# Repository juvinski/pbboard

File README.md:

# PocketBeagle 2 DIY Cape for Ardupilot
This project aim enable to run [Ardupilot](https://ardupilot.org/) on the [PocketBeagle 2](https://www.beagleboard.org/boards/pocketbeagle-2) Board.

# Board manufacturing
## PCBWay
I'm using the PCBWay to produce the boards - 5 boards have a cost of USD 5.00
You can use [this file](Board_Archives_Manufacturing/PocketPilot2.kicad_pcb.zip).

## Other Services
I believe the same file can be used by other online PCB manufactures.

# Board Images
## Board Only

## Board Components - Preview

# Hardware instructions
## Board manufacturing
### Board version 1.1

### Soldering resistors, transistor and rc output headers 

### Soldering output headers 

### Soldering Pocketbeagle 2 headers

### Soldering Leds

### Preparing the IMU - using double sided tape

### Soldering the IMU

### Finished

## Schematic
The schematic can be found [here](Schematic/PocketPilot2.pdf).

## Parts
	- 1 IMU [GY-912](https://www.ebay.com/itm/166809278501)
	- 4 Resistors 1KΩ
	- 2 Resistors 10k 0.1%
	- 2 Resistors 20k 0.1%
	- 3 Led Red, Blue and Green color 
	- 1 BC548 NPN Transistor
	- 1 I2C Digital [Power Module/Monitor](https://ardupilot.org/copter/docs/common-powermodule-landingpage.html#i2c-power-monitor)
	- 6 Pin header 1 x 5 straight
	- 3 Pin header 1 x 4 straight
	- 1 Pin header 1 x 6 straight
	- 6 Pin header 1 x 3 straight or 90°
	- 1 Pin header 1 x 2 straight
	- 1 Pin header female 1 x 8 - optional

## Details
To use the I2C power sensing you can use the [Holybro PM2D](https://holybro.com/products/pm02d-power-module?srsltid=AfmBOoraJGVR_kFEiSwKRgzMLQZ1dEZXMhWgGvN6DEnkXQVvNgj2pTN2).
The analog power sensing is using 4 resistors.
The outputs of the sensor was changed by a female reader and both 5Volts output connectec together as the GND.
The GY-912 is soldered direct over the board once the PocketBeagle 2 is over it and the space between the PocketBeagle 2 board and the DIY board it's small.
Once the Kicad project is shared, you can modify freely according your needs.
The CAN interface need a CAN Transceiver breadboard like CJMCU-1051 (or any TJA1051) with 3.3Volts interface for TX and RX.
The buzzer circuit is simple but powerfull.
For the USB OTG you are free to use what kind of USB is more suitable for you. The board export 5 pins there the 4th is not connected.

## Board details
	- 4 UARTs - One have the I2C to be used with a GPS + Compass
 	- 3 I2Cs - One is under the Power header, Other in the GPS header and one for I2C
  	- 4 GPIO pins with GND
	- Support for I2C and/or Power Sensing
   	- 6 Outputs
   	- Buzzer output for an Active buzzer
*** All pins is just 3.3 Volts ***  
*** 5 Volts will brick your PocketBeagle 2 ***

# Software Instructions
The software instructions can be found at [Ardupilot Wiki] (https://github.com/juvinski/ardupilot_wiki/blob/pocket2/common/source/docs/common-pocketbeagle-2.rst).
This version will be present in Ardupilot official wiki when the version 4.7 release.

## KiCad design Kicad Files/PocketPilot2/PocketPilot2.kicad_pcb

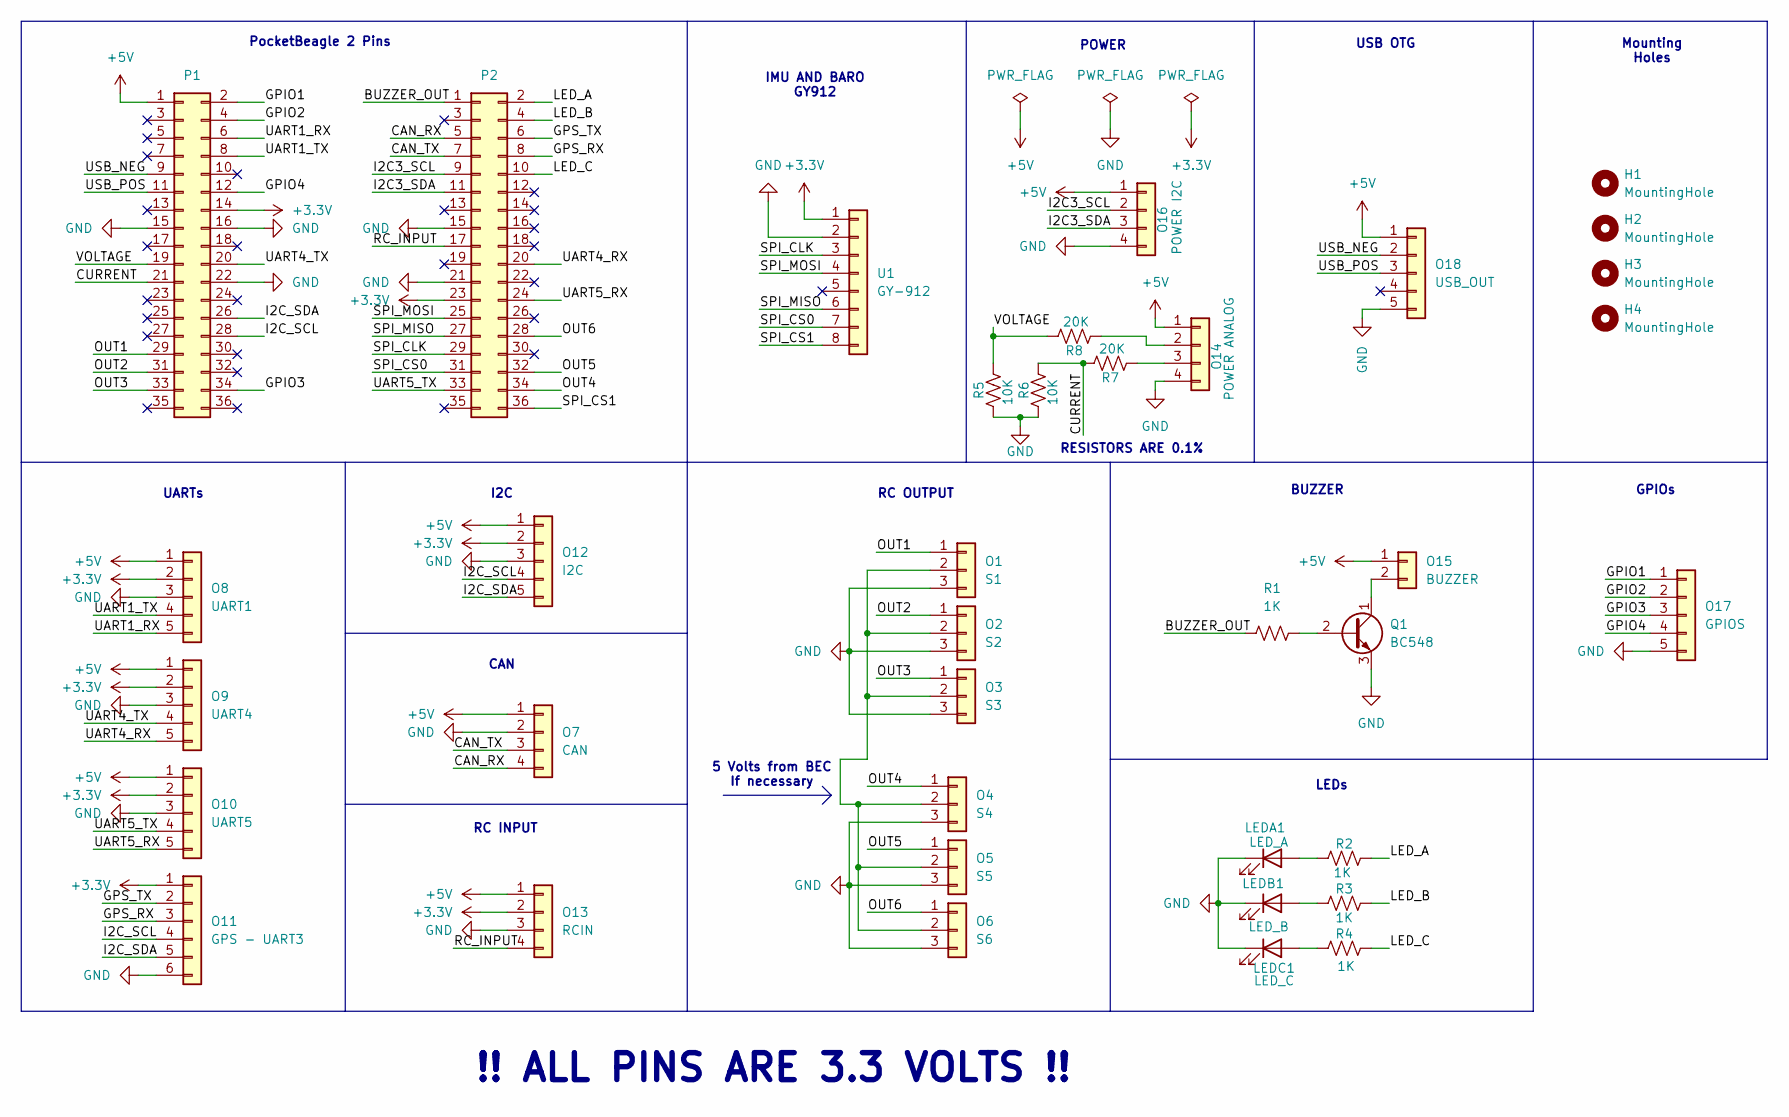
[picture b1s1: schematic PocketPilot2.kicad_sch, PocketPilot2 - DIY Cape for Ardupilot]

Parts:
H1, H2, H3, H4: MountingHole; MountingHole_2.7mm_M2.5
LEDA1: LED_A; LED_D3.0mm
LEDB1: LED_B; LED_D3.0mm
LEDC1: LED_C; LED_D3.0mm
O1: S1; PinHeader_1x03_P2.54mm_Vertical
O2: S2; PinHeader_1x03_P2.54mm_Vertical
O3: S3; PinHeader_1x03_P2.54mm_Vertical
O4: S4; PinHeader_1x03_P2.54mm_Vertical
O5: S5; PinHeader_1x03_P2.54mm_Vertical
O6: S6; PinHeader_1x03_P2.54mm_Vertical
O7: CAN; PinHeader_1x04_P2.54mm_Vertical
O8: UART1; PinHeader_1x05_P2.54mm_Vertical
O9: UART4; PinHeader_1x05_P2.54mm_Vertical
O10: UART5; PinHeader_1x05_P2.54mm_Vertical
O11: GPS - UART3; PinHeader_1x06_P2.54mm_Vertical
O12: I2C; PinHeader_1x05_P2.54mm_Vertical
O13: RCIN; PinHeader_1x04_P2.54mm_Vertical
O14: POWER ANALOG; PinHeader_1x04_P2.54mm_Vertical
O15: BUZZER; PinHeader_1x02_P2.54mm_Vertical
O16: POWER I2C; PinHeader_1x04_P2.54mm_Vertical
O17: GPIOS; PinHeader_1x05_P2.54mm_Vertical
O18: USB_OUT; PinHeader_1x05_P2.54mm_Vertical
P1, P2: Conn_02x18_Odd_Even; PinHeader_2x18_P2.54mm_Vertical
Q1: BC548; TO-92_Inline
R1: 1K; R_Axial_DIN0204_L3.6mm_D1.6mm_P5.08mm_Horizontal
R2, R3, R4: 1K; R_Axial_DIN0204_L3.6mm_D1.6mm_P2.54mm_Vertical
R5, R6: 10K; R_Axial_DIN0204_L3.6mm_D1.6mm_P5.08mm_Horizontal
R7, R8: 20K; R_Axial_DIN0204_L3.6mm_D1.6mm_P5.08mm_Horizontal
U1: GY-912; PinSocket_1x08_P2.54mm_Vertical

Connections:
+3.3V: O8.2, O9.2, O10.2, O11.1, O12.2, O13.2, P1.14, P2.23, U1.1
+5V: O7.1, O8.1, O9.1, O10.1, O12.1, O13.1, O14.1, O15.1, O16.1, O18.1, P1.1
/BUZZER_OUT: P2.1, R1.1
/CAN_RX: O7.4, P2.5
/CAN_TX: O7.3, P2.7
/CURRENT: P1.21, R6.2, R7.2
/GPIO1: O17.1, P1.2
/GPIO2: O17.2, P1.4
/GPIO3: O17.3, P1.34
/GPIO4: O17.4, P1.12
/GPS_RX: O11.3, P2.8
/GPS_TX: O11.2, P2.6
/I2C3_SCL: O16.2, P2.9
/I2C3_SDA: O16.3, P2.11
/I2C_SCL: O11.4, O12.4, P1.28
/I2C_SDA: O11.5, O12.5, P1.26
/LED_A: P2.2, R2.2
/LED_B: P2.4, R3.2
/LED_C: P2.10, R4.2
/OUT1: O1.1, P1.29
/OUT2: O2.1, P1.31
/OUT3: O3.1, P1.33
/OUT4: O4.1, P2.34
/OUT5: O5.1, P2.32
/OUT6: O6.1, P2.28
/RC_INPUT: O13.4, P2.17
/SPI_CLK: P2.29, U1.3
/SPI_CS0: P2.31, U1.7
/SPI_CS1: P2.36, U1.8
/SPI_MISO: P2.27, U1.6
/SPI_MOSI: P2.25, U1.4
/UART1_RX: O8.5, P1.6
/UART1_TX: O8.4, P1.8
/UART4_RX: O9.5, P2.20
/UART4_TX: O9.4, P1.20
/UART5_RX: O10.5, P2.24
/UART5_TX: O10.4, P2.33
/USB_NEG: O18.2, P1.9
/USB_POS: O18.3, P1.11
/VOLTAGE: P1.19, R5.2, R8.2
GND: LEDA1.1 (K), LEDB1.1 (K), LEDC1.1 (K), O1.3, O2.3, O3.3, O4.3, O5.3, O6.3, O7.2, O8.3, O9.3, O10.3, O11.6, O12.3, O13.3, O14.4, O16.4, O17.5, O18.5, P1.15, P1.16, P1.22, P2.15, P2.21, Q1.3 (E), R5.1, R6.1, U1.2
unnamed: LEDA1.2 (A), R2.1
unnamed: LEDB1.2 (A), R3.1
unnamed: LEDC1.2 (A), R4.1
unnamed: O1.2, O2.2, O3.2, O4.2, O5.2, O6.2
unnamed: O14.2, R8.1
unnamed: O14.3, R7.1
unnamed: O15.2, Q1.1 (C)
unnamed: Q1.2 (B), R1.2

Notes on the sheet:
RC OUTPUT
IMU AND BARO GY912
LEDs
Mounting Holes
I2C
UARTs
BUZZER
RC INPUT
POWER
5 Volts from BEC If necessary
RESISTORS ARE 0.1%
!! ALL PINS ARE 3.3 VOLTS !!
GPIOs
PocketBeagle 2 Pins
CAN
USB OTG

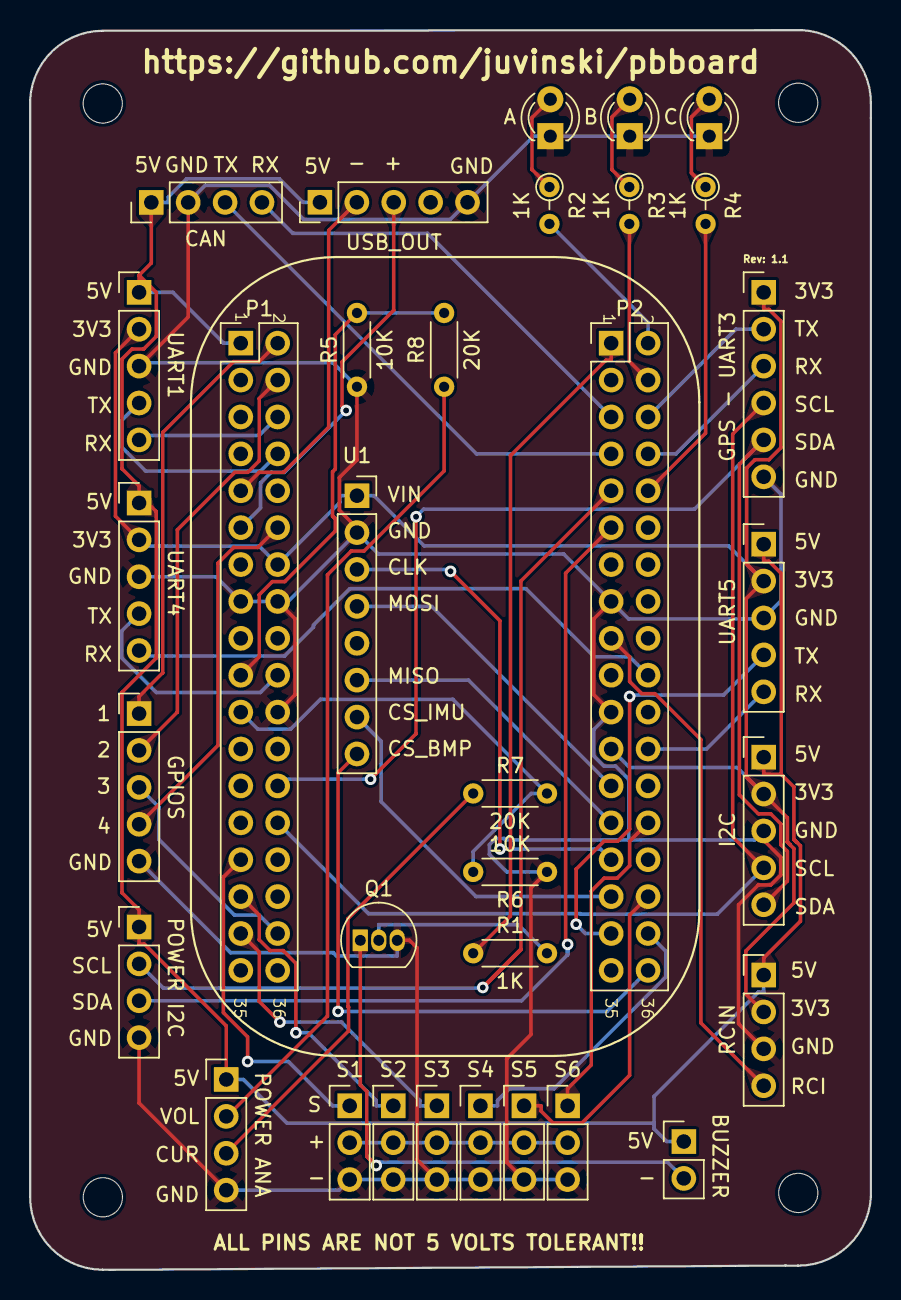
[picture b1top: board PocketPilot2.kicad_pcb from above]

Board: 2 copper layers, 57.9 x 85.3 mm, 37 parts (0 on the bottom side), 49 nets.

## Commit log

2025-06-30 Update README.md
    Initial commit
2025-07-03 Commit inicial
2025-07-03 Update board details
2025-07-11 Update to version to 1.1 Update GPIO pins
2025-11-02 Version 1.2 release Update board to add analog power sensing. Update images and instructions.
2025-11-02 Fix image names
